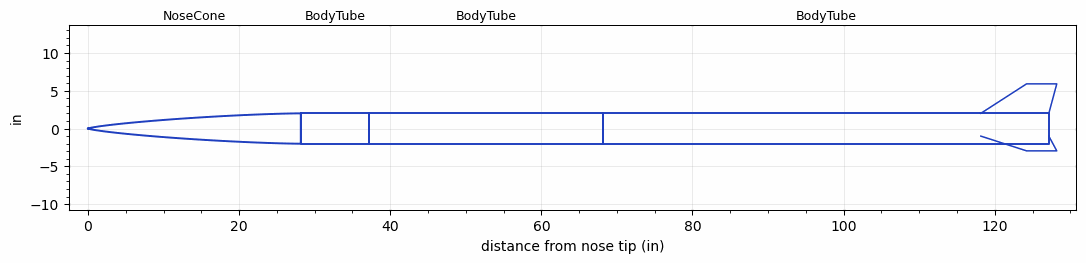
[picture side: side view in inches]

<RASAeroDocument>
 <FileVersion>2</FileVersion>
 <RocketDesign>
  <NoseCone>
   <Length>28.16</Length>
   <Diameter>4.02</Diameter>
   <Shape>Von Karman Ogive</Shape>
   <Location>0</Location>
  </NoseCone>
  <BodyTube>
   <Length>9</Length>
   <Diameter>4.02</Diameter>
   <Location>28.16</Location>
   <Protuberance>
    <StreamlinedNoBaseDrag>0</StreamlinedNoBaseDrag>
    <StreamlinedWithBaseDrag>0</StreamlinedWithBaseDrag>
    <InclinedPlate1Angle>90</InclinedPlate1Angle>
    <InclinedPlate1FrontalArea>0.276</InclinedPlate1FrontalArea>
    <InclinedPlate2Angle>0</InclinedPlate2Angle>
    <InclinedPlate2FrontalArea>0</InclinedPlate2FrontalArea>
   </Protuberance>
  </BodyTube>
  <BodyTube>
   <Length>31</Length>
   <Diameter>4.02</Diameter>
   <Location>37.16</Location>
  </BodyTube>
  <BodyTube>
   <Length>59</Length>
   <Diameter>4.02</Diameter>
   <RailGuideDiameter>0.5</RailGuideDiameter>
   <RailGuideHeight>0.5</RailGuideHeight>
   <Location>68.16</Location>
   <Fin>
    <Count>3</Count>
    <Chord>9</Chord>
    <Span>3.9</Span>
    <SweepDistance>6.0516</SweepDistance>
    <TipChord>4</TipChord>
    <Thickness>0.352</Thickness>
    <LERadius>0.08</LERadius>
    <Location>9</Location>
    <AirfoilSection>Hexagonal</AirfoilSection>
    <FX1>0.4</FX1>
    <FX3>0.2</FX3>
   </Fin>
   <Protuberance>
    <StreamlinedNoBaseDrag>0</StreamlinedNoBaseDrag>
    <StreamlinedWithBaseDrag>1.5</StreamlinedWithBaseDrag>
    <InclinedPlate1Angle>0</InclinedPlate1Angle>
    <InclinedPlate1FrontalArea>0</InclinedPlate1FrontalArea>
    <InclinedPlate2Angle>0</InclinedPlate2Angle>
    <InclinedPlate2FrontalArea>0</InclinedPlate2FrontalArea>
   </Protuberance>
  </BodyTube>
  <Surface>Smooth Paint</Surface>
  <ModifiedBarrowman>False</ModifiedBarrowman>
  <Turbulence>False</Turbulence>
  <UseBooster1>False</UseBooster1>
  <UseBooster2>False</UseBooster2>
 </RocketDesign>
 <LaunchSite>
  <Altitude>0</Altitude>
  <Pressure>0</Pressure>
  <RodAngle>6</RodAngle>
  <RodLength>17</RodLength>
  <Temperature>100</Temperature>
  <WindSpeed>10</WindSpeed>
 </LaunchSite>
 <Recovery>
  <Altitude1>1000</Altitude1>
  <Altitude2>1000</Altitude2>
  <DeviceType1>None</DeviceType1>
  <DeviceType2>None</DeviceType2>
  <Event1>False</Event1>
  <Event2>False</Event2>
  <Size1>1</Size1>
  <Size2>1</Size2>
  <EventType1>None</EventType1>
  <EventType2>None</EventType2>
  <CD1>1.33</CD1>
  <CD2>1.33</CD2>
 </Recovery>
 <SimulationList>
  <Simulation>
   <SustainerEngine>N5800-CS  (CTI)</SustainerEngine>
   <SustainerLaunchWt>61.93</SustainerLaunchWt>
   <SustainerNozzleDiameter>3</SustainerNozzleDiameter>
   <SustainerCG>84.55</SustainerCG>
   <SustainerIgnitionDelay>0</SustainerIgnitionDelay>
   <Booster1SeparationDelay>0</Booster1SeparationDelay>
   <Booster1IgnitionDelay>0</Booster1IgnitionDelay>
   <IncludeBooster1>False</IncludeBooster1>
   <Booster2Delay>0</Booster2Delay>
   <IncludeBooster2>False</IncludeBooster2>
   <TimetoApogee>38.28958</TimetoApogee>
   <MaxAltitude>29412.29</MaxAltitude>
   <MaxVelocity>2327.705</MaxVelocity>
  </Simulation>
 </SimulationList>
</RASAeroDocument>
